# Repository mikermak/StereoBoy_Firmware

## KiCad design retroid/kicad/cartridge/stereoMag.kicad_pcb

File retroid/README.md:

# StereoBoy – Retroid build

A ready-to-order build of [iamericmin's StereoBoy](https://github.com/iamericmin/StereoBoy_Firmware) ([Hackaday](https://hackaday.io/project/205771-stereoboy)), prepared in October 2026. **Not ordered yet** — this folder holds everything needed to pick it up again.

## What changed compared to the original

| Area | Change |
|---|---|
| Firmware | `src/hw_config.c` reads the cartridge SD card over **SPI1** (CS = GPIO2), matching the published StereoMag cartridge. SDIO stays available with `-DSB_SD_SDIO=ON`. Prebuilt: [`firmware/StereoBoy_FW_sd-spi.uf2`](firmware/) (builds, not yet tested on hardware). |
| Board look | White solder mask + JLCPCB **multi-colour silkscreen**: black board, red tracks, gold pads. Signatures, quote, bear logo and "ENGINEERING PROTOTYPE" removed; **RETROID** logo added on both sides, plus a "based on StereoBoy by iamericmin" credit. Electrically unchanged (KiCad DRC: 0 unconnected, 0 schematic-parity issues). |
| KiCad | [`kicad/hoofdprint/`](kicad/hoofdprint/) is the branded main board (KiCad 10). The drill/place origin is set to the board's bottom-left corner so the Gerbers line up with the EasyEDA colour files. |
| Parts | BOM fixed against the designer's own parts lists. Notable: TPS61090 (not TPS61092), SN74HC165**PWR** (TSSOP footprint), FM24**CL**64B (3.3 V), APX803S-31, VS1053B. Out-of-stock parts replaced (see `BESTELLEN.md`). |

## Folder contents

- `productie/hoofdprint/gerbers_hoofdprint_KLEUR.zip` – KiCad Gerbers + the four `Fabrication_Colorful*` files from EasyEDA Pro. Upload this one.
- `productie/hoofdprint/JLCPCB_BOM.csv`, `JLCPCB_CPL.csv` – 70 BOM lines / 184 placements, every line has a verified LCSC number. VR1 (thumb wheel) and D17 (RGB LED) are left out on purpose (hand-solder / optional).
- `productie/cartridge/` – StereoMag dev-kit cartridge (2 layers, 1.0 mm): Gerbers, BOM, CPL.
- `artwork/` – 1200 dpi colour artwork (exact board size), previews, the RETROID wordmark, outline DXFs, and the EasyEDA colour files.
- `scripts/` – how the artwork was made: KiCad SVG plots → PNG (`colorart.py`, `colorart_brand.py`), and `origin_dxf.py` (aux origin + outline DXF).
- `BESTELLEN.md` – step-by-step JLCPCB checklist (Dutch).
- `StereoBoy_bestellijst.xlsx` – full parts list, cartridge, enclosure/donor-GBP parts, known issues (Dutch).

## JLCPCB settings that matter

4 layers · **1.0 mm** · White · **ENIG 1U** · min via **0.2 mm** · Advanced Options → Silkscreen Technology → **EasyEDA multi-color silkscreen** · Confirm Production File: Yes · PCBA Standard, **both sides**, qty 2, Confirm Parts Placement: Yes. Tick J7 (USB-C) by hand in the BOM step — JLC deselects it ("processing difficult").

Quote on 1 Oct 2026: **$387.77** (PCB $84.83 + PCBA $302.94, excl. shipping). Most of it is one-off cost (setup, stencil, fixture, ~$107 extended-part feeder fees), so 5 assembled boards cost far less per unit than 2. Swapping ~10 passives to JLC "Basic" parts would save roughly $25–35.

## Still open

- **Music library script.** The firmware expects `.artists.sbc` / `.albums.sbc` / `.tracks.sbc` (+ `artwork.lut/bin`) on the SD card; the generator script is not in the original repo.
- Colour silkscreen + KiCad Gerbers is not an official JLC flow: check the colours in JLC's production-file preview before approving.
- Cartridge DRC: I2S_WSEL/BCLK swapped at the 2×10 dev header and the reset RC unconnected — harmless unless J2 is used.

## Licensing note

The upstream repository has no licence file. The cartridge KiCad files come from the designer's [Hackaday files page](https://hackaday.io/project/205771/files). All credit for the hardware and firmware goes to iamericmin and team; RETROID branding is ours.

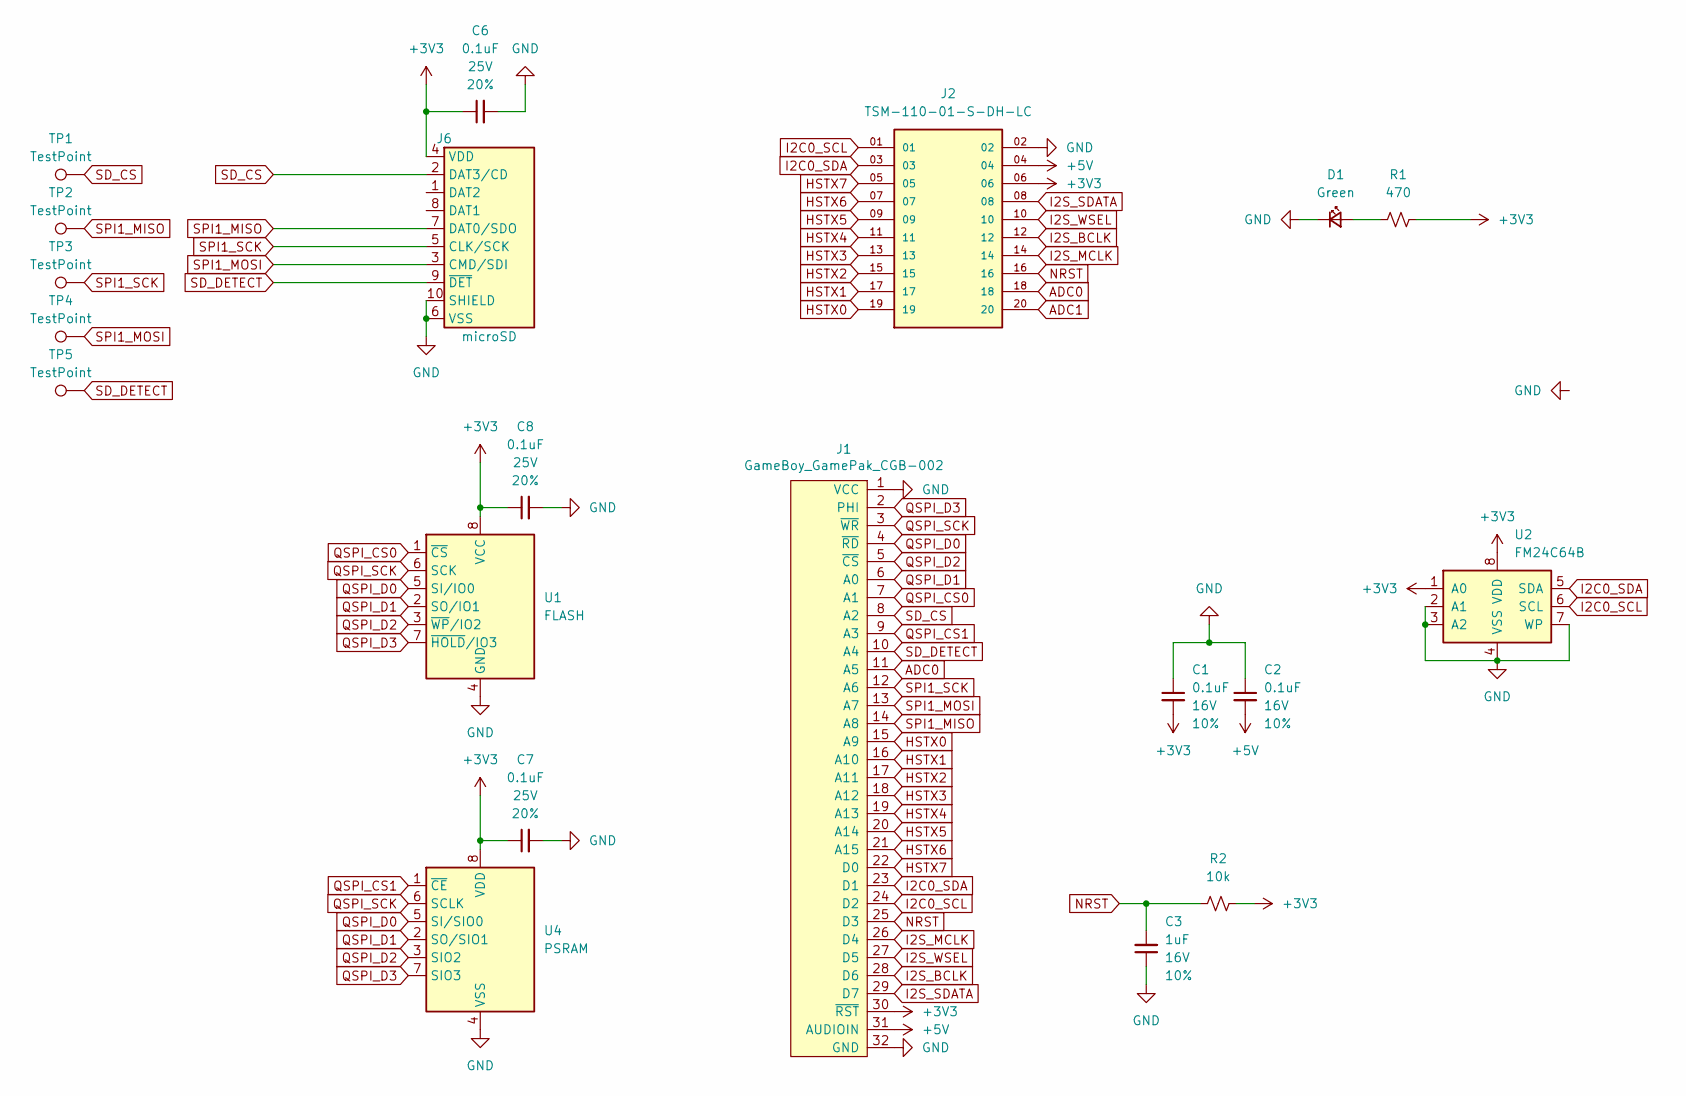
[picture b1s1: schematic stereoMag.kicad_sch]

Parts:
C1, C2: 0.1uF; C_1206_3216Metric; Voltage 16V; Tolerance 10%
C3: 1uF; C_0603_1608Metric; Voltage 16V; Tolerance 10%
C6, C7, C8: 0.1uF; C_0603_1608Metric; Voltage 25V; Tolerance 20%
D1: Green; LED_0603_1608Metric_Green
J1: GameBoy_GamePak_CGB-002; GameBoy_GamePak_CGB-002_P1.50mm_Edge
J2: TSM-110-01-S-DH-LC; SAMTEC_TSM-110-01-S-DH-LC; PARTREV R
J6: microSD; microSD_External_Pin
R1: 470; R_0603_1608Metric
R2: 10k; R_0603_1608Metric
TP1, TP2, TP3, TP4, TP5: TestPoint; TestPoint_Pad_D1.0mm
U1: FLASH; SOIC-8_3.9x4.9mm_P1.27mm
U2: FM24C64B; SOIC-8_3.9x4.9mm_P1.27mm
U4: PSRAM; SOIC-8_3.9x4.9mm_P1.27mm

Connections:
+3V3: C1.2, C6.1, C7.1, C8.1, J1.30 (~RST), J2.06, J6.4 (VDD), R1.2, R2.2, U1.8 (VCC), U2.1 (A0), U2.8 (VDD), U4.8 (VDD)
+5V: C2.2, J1.31 (AUDIOIN), J2.04
ADC0: J1.11 (A5), J2.18
ADC1: J2.20
GND: C1.1, C2.1, C3.1, C6.2, C7.2, C8.2, D1.1 (K), J1.1 (VCC), J1.32 (GND), J2.02, J6.6 (VSS), J6.10 (SHIELD), U1.4 (GND), U2.2 (A1), U2.3 (A2), U2.4 (VSS), U2.7 (WP), U4.4 (VSS)
HSTX0: J1.15 (A9), J2.19
HSTX1: J1.16 (A10), J2.17
HSTX2: J1.17 (A11), J2.15
HSTX3: J1.18 (A12), J2.13
HSTX4: J1.19 (A13), J2.11
HSTX5: J1.20 (A14), J2.09
HSTX6: J1.21 (A15), J2.07
HSTX7: J1.22 (D0), J2.05
I2C0_SCL: J1.24 (D2), J2.01, U2.6 (SCL)
I2C0_SDA: J1.23 (D1), J2.03, U2.5 (SDA)
I2S_BCLK: J1.28 (D6), J2.12
I2S_MCLK: J1.26 (D4), J2.14
I2S_SDATA: J1.29 (D7), J2.08
I2S_WSEL: J1.27 (D5), J2.10
NRST: C3.2, J1.25 (D3), J2.16, R2.1
unnamed: D1.2 (A), R1.1
QSPI_CS0: J1.7 (A1), U1.1 (~CS)
QSPI_CS1: J1.9 (A3), U4.1 (~CE)
QSPI_D0: J1.4 (~RD), U1.5 (SI/IO0), U4.5 (SI/SIO0)
QSPI_D1: J1.6 (A0), U1.2 (SO/IO1), U4.2 (SO/SIO1)
QSPI_D2: J1.5 (~CS), U1.3 (~WP/IO2), U4.3 (SIO2)
QSPI_D3: J1.2 (PHI), U1.7 (~HOLD/IO3), U4.7 (SIO3)
QSPI_SCK: J1.3 (~WR), U1.6 (SCK), U4.6 (SCLK)
SD_CS: J1.8 (A2), J6.2 (DAT3/CD), TP1.1
SD_DETECT: J1.10 (A4), J6.9 (~DET), TP5.1
SPI1_MISO: J1.14 (A8), J6.7 (DAT0/SDO), TP2.1
SPI1_MOSI: J1.13 (A7), J6.3 (CMD/SDI), TP4.1
SPI1_SCK: J1.12 (A6), J6.5 (CLK/SCK), TP3.1

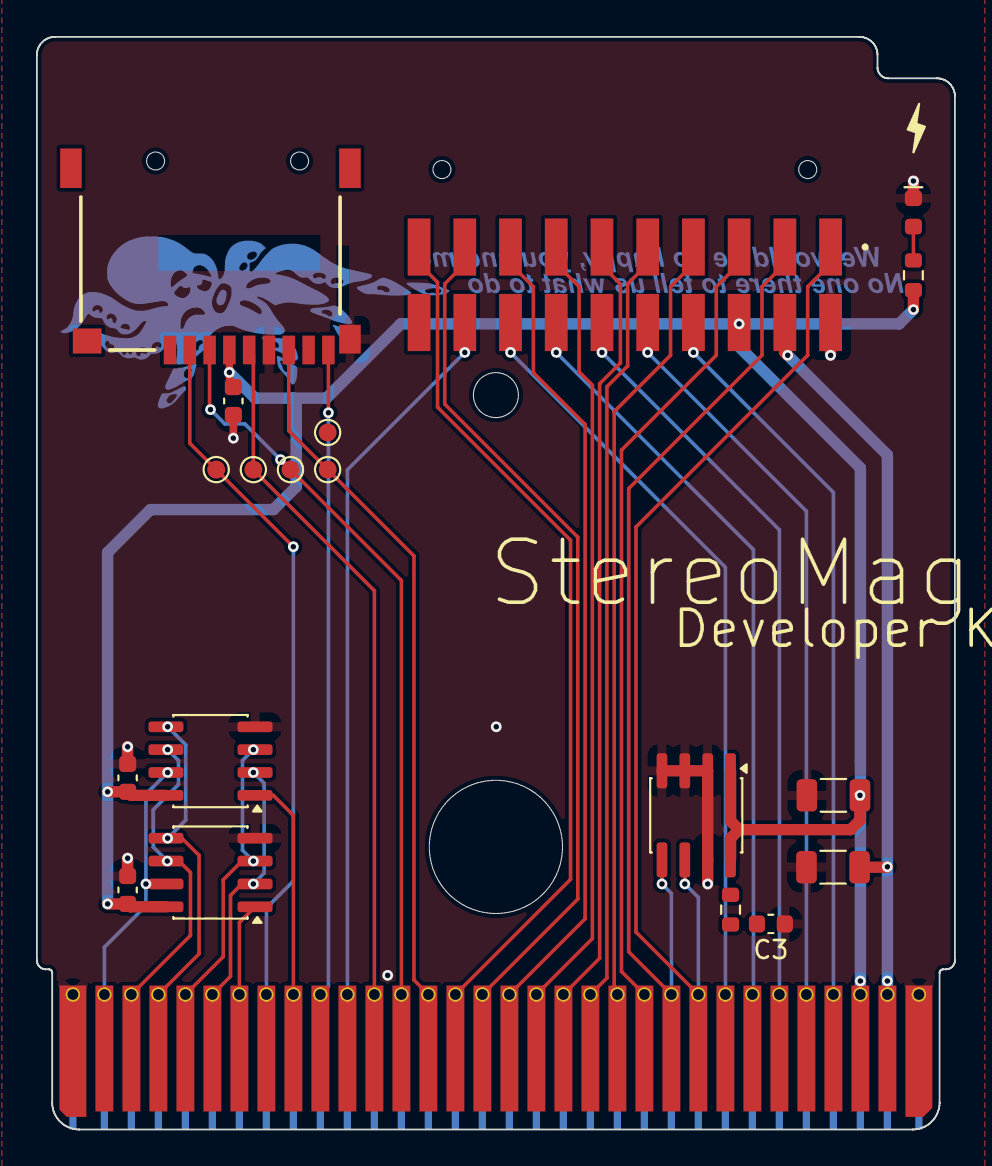
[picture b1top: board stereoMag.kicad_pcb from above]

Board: 2 copper layers, 51.0 x 60.7 mm, 20 parts (0 on the bottom side), 32 nets.

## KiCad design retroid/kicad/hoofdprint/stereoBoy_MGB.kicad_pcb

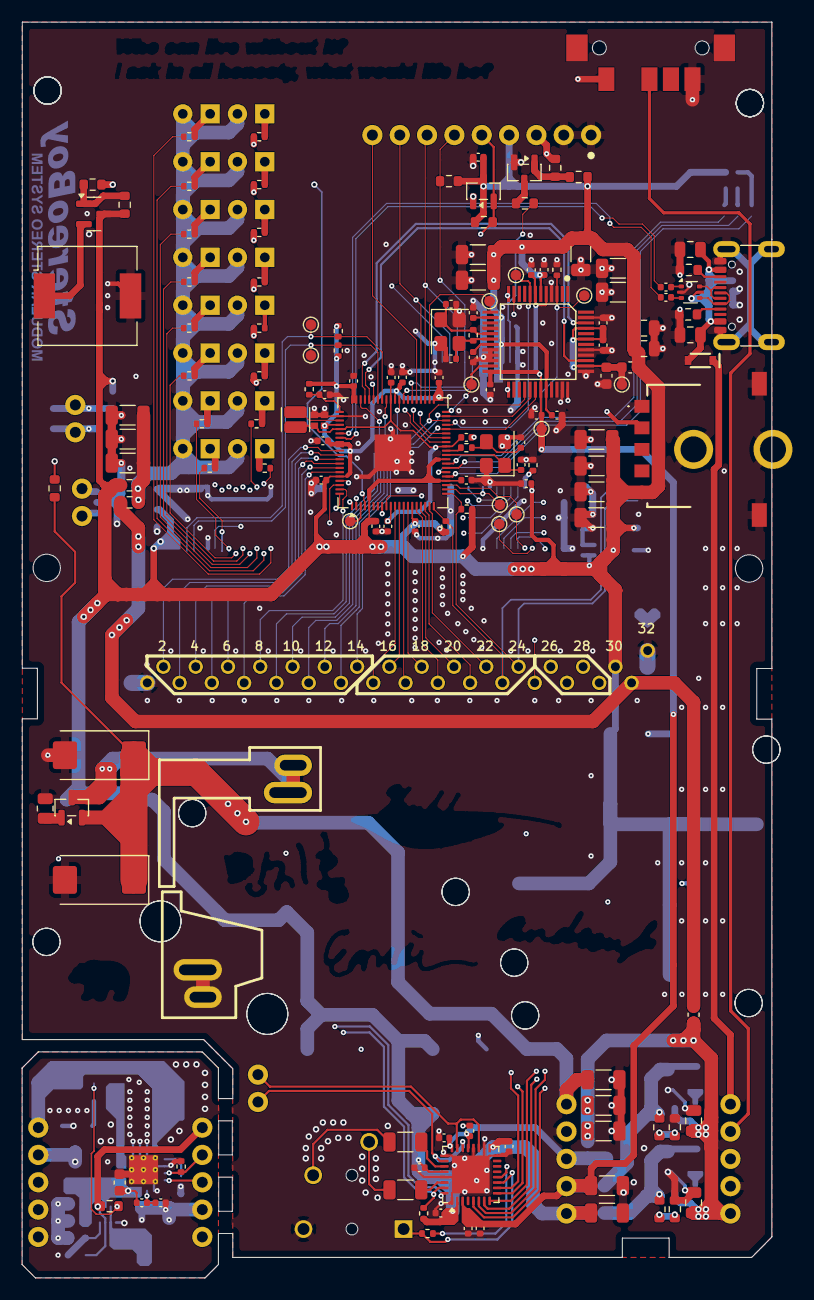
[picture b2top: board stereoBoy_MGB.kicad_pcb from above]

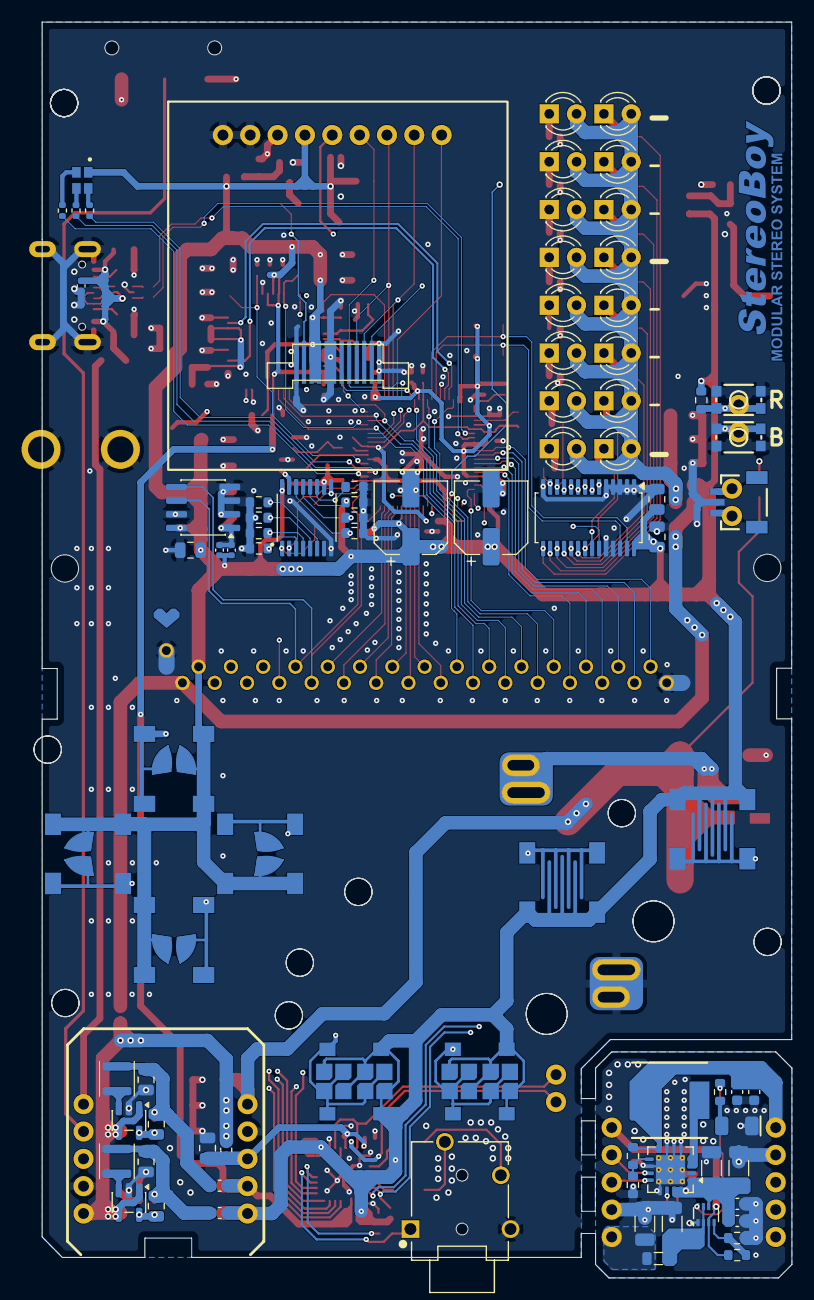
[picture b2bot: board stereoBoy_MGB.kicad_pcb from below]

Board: 4 copper layers, 69.7 x 116.7 mm, 249 parts (84 on the bottom side), 165 nets.

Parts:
+0: MGB+BATTERY4
-0: MGB-BATTERY4
BTN_A1: GameBoy_ButtonPad; GameBoy_A_B_Pad
BTN_B1: GameBoy_ButtonPad; GameBoy_A_B_Pad
BTN_D1: GameBoy_ButtonPad; GameBoy_DPad
BTN_L1: GameBoy_ButtonPad; GameBoy_DPad
BTN_R1: GameBoy_ButtonPad; GameBoy_DPad
BTN_U1: GameBoy_ButtonPad; GameBoy_DPad
BZ1: Buzzer; Buzzer_CUI_CPT-9019S-SMT
C1: 100uF; CP_EIA-7343-15_Kemet-W_HandSolder
C2: 47uF; CP_EIA-7343-15_Kemet-W_HandSolder
C3, C4: 10pF; C_0402_1005Metric
C5, C6, C15, C16, C17, C18, C19, C22, C23, C25, C26, C37, C47, C49, C52, C57, C58, C60, C75, C79: 0.1uF; C_0402_1005Metric
C7, C54, C85: 0.1uF; C_0603_1608Metric
C8: 10uF; C_1206_3216Metric
C9, C11: 4.7uF; C_0805_2012Metric
C10, C12: 6.8pF; C_0805_2012Metric
C13, C24, C27, C31, C36, C38, C39, C40, C41, C71: 1.0uF; C_0402_1005Metric
C14: 4.7uF; C_0402_1005Metric
C20, C21: 15pF; C_0402_1005Metric
C28: 100uF; C_0603_1608Metric
C29, C61, C64, C68, C69, C76, C87: 1.0uF; C_0805_2012Metric
C30, C86: 10uF; C_0805_2012Metric
C32, C33, C48, C53, C62, C77, C78, C80: 100uF; C_1206_3216Metric
C34, C42, C45, C46, C51, C55, C56, C66, C67, C70, C72, C73, C74, C88: 1.0uF; C_1206_3216Metric
C43, C44: 10uF; CP_Elec_6.3x4.5
C59: 0.1uF; C_0805_2012Metric
C63: 2.2uF; C_0603_1608Metric
C65: 10uF; C_0603_1608Metric
C81: 0.1uF; WAi_0402_1005Metric
C82: 4.7uF; WAi_0402_1005Metric
C83, C84: 22.1uF; C_0402_1005Metric
D1, D2, D3, D4, D5, D6, D7, D8, D9, D10, D11, D12, D13, D14, D15, D16: LED; LED_D3.0mm
D17: CLMVC-FKA-CL1D1L71BB7C3C3; CREE_LED_2mm_x_2mm_Common_Anode
D22: BAT60JFILM; SOD-323
D23: Green; LED_1206_3216Metric_Green
J1: Conn_01x12; 1.54_IPS_FPC_Solder
J2: JST_1mm_3_Vertical; JST_1x03_P1.0mm_Horizontal_SMD
J3: GameBoy_Cartridge; MGB-CART-CONN
J4, J8: Conn_01x02; 1x02_P2.54mm
J5: SJ-43514; SJ_43514
J6: Conn_01x09; 1x09_P2.54mm
J7: USB_C_Receptacle_USB2.0_16P; USB_C_Receptacle_GCT_USB4105-xx-A_16P_TopMnt_Horizontal
J10, J11: Conn_01x05; 1x05_P2.54mm
J13: Conn_01x10; StereoBoy_PSU
L1: 6.8uH; Inductor_7.3x6.6mm
L2, L6, L8: 600Ω @ 100MHz; C_0603_1608Metric
L3, L7: 600Ω @ 100MHz; L_0603_1608Metric
L4, L5: 2.2uH; L_APV_ANR3012
L9: 3.3uH; L_Cenker_CKCS201610
L10: 600Ω @ 100MHz; L_0805_2012Metric
Q1: DMG2301L; SOT-23
Q2: FDN306P; SOT-23
Q3: BSS138; SOT-23
R1: 500k; R_0603_1608Metric
R2: 330; R_0603_1608Metric
R3: 390k; R_0603_1608Metric
R4: 1.62M; C_0402_1005Metric
R5, R6, R7, R8, R9, R10, R11, R12, R20, R24, R27, R29, R34, R39: 10k; R_0603_1608Metric
R13: 180k; C_0402_1005Metric
R14, R15: 27; C_0402_1005Metric
R16, R33: 5.1k; R_0603_1608Metric
R17, R18, R19: 330; R_0402_1005Metric
R21, R22, R23: 0; R_0603_1608Metric
R25: 33; R_0402_1005Metric
R26, R49: 1k; R_0402_1005Metric
R28: 10; R_0603_1608Metric
R30, R54: 10K; R_0402_1005Metric
R31: 1k; R_0603_1608Metric
R32, R58, R59, R60, R61, R62, R63, R64, R65, R66, R67, R68, R69, R70, R71, R72: 220; R_0402_1005Metric
R35: 453k; R_0603_1608Metric
R36, R38: 100k; R_0603_1608Metric
R37: 200k; R_0603_1608Metric
R44: 100k; R_0805_2012Metric
R45, R46, R47, R48: 2.2K; R_0402_1005Metric
R50: 100K; R_0402_1005Metric
R51: 1M; R_0402_1005Metric
R53: 2.2k; R_0402_1005Metric
R55, R56: 1.4M; R_0603_1608Metric
R73: 220; R_0603_1608Metric
SELECT1: SMD_6x3.5mm_h2.5mm; GameBoy_Select_Start
SPK_CONN1: Conn_01x02; 1x02
START1: SMD_6x3.5mm_h2.5mm; GameBoy_Select_Start
SW1, SW2: SMD_4.6x2.8mm_h2.5mm; Push_SMD_4.6x2.8mm_h2.5mm
SW3: MGB-SW1; GBP_Power_Switch
TP1, TP2, TP10, TP12, TP23, TP24, TP26, TP27, TP31, TP32, TP33: TestPoint_Alt; TestPoint_Pad_D1.0mm
TP14: TestPoint; TestPoint_Pad_D1.0mm
U1: CODECODER-VS1053B_LQFP48_; VS1053b
U2: PCA9685PW; TSSOP-28_4.4x9.7mm_P0.65mm
U3: TPS61090; Texas_RSA_VQFN-16-1EP_4x4mm_P0.65mm_EP2.7x2.7mm_ThermalVias
U4, U8: TLV62569DBV; SOT-23-5
U5: APX803; SOT-23
U6: 74HC165; TSSOP-16_4.4x5mm_P0.65mm
U7: TPS2116DRL; SOT-583-8
U10: TLV320AIC3100; VQFN-32-1EP_5x5mm_P0.5mm_EP3.5x3.5mm
U11: RP2350B; QFN-80-1EP_10x10mm_P0.4mm_EP3.4x3.4mm
U12: USBLC6-2P6; SOT-666
U14: FM24C64C; SOIC-8_3.9x4.9mm_P1.27mm
UNK_HOLE_0: dummyfp0
UNK_HOLE_1: dummyfp1
UNK_HOLE_4: dummyfp4
UNK_HOLE_5: dummyfp5
UNK_HOLE_6: dummyfp6
UNK_HOLE_7: dummyfp7
UNK_HOLE_8: dummyfp8
UNK_HOLE_9: dummyfp9
UNK_HOLE_10: dummyfp10
UNK_HOLE_11: dummyfp11
UNK_HOLE_12: dummyfp12
VR1: RK10J11R0A0L
Y1, Y2: 12MHz; Crystal_SMD_3225-4Pin_3.2x2.5mm

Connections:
+1V2: C22.1, C23.1, C25.1, C82.1, L9.1, U11.10 (DVDD), U11.32 (DVDD), U11.51 (DVDD), U11.65 (VREG_FB)
+1V8: C24.2, C26.2, C31.2, C39.2, C40.2, C80.1, J13.2, L6.2, TP26.1, U1.5 (CVDD0), U1.7 (CVDD1), U1.24 (CVDD2), U1.31 (CVDD3), U10.3 (DVDD)
+3V3: BTN_A1.1, BTN_B1.1, BTN_D1.1, BTN_L1.1, BTN_R1.1, BTN_U1.1, C6.2, C13.2, C15.2, C16.1, C17.1, C18.1, C19.1, C27.2, C29.2, C36.2, C37.2, C38.2, C41.2, C43.1, C44.1, C46.2, C47.1, C51.2, C52.1, C55.2, C57.1, C58.1, C59.1, C60.1, C61.2, C64.1, C66.2, C67.2, C69.2, C70.2, C71.2, C72.2, C73.2, C74.2, C78.1, C79.1, C81.2, D17.1, J1.3, J1.4, J3.30 (~RES), J6.6, J13.1, L2.2, L8.1, Q1.3 (D), R20.2, R22.1, R24.1, R25.1, R27.2, R29.2, R30.2, R34.1, R45.2, R46.1, R47.2, R48.1, SELECT1.1, START1.1, U1.6 (IOVDD0), U1.14 (IOVDD1), U1.19 (IOVDD2), U1.32 (XTEST), U2.28 (VDD), U5.3 (VCC), U6.16 (VCC), U10.2 (IOVDD), U10.17 (AVDD), U10.28 (HPVDD), U11.5 (IOVDD), U11.15 (IOVDD), U11.24 (IOVDD), U11.29 (IOVDD), U11.41 (IOVDD), U11.50 (IOVDD), U11.59 (ADC_AVDD), U11.60 (IOVDD), U11.64 (VREG_VIN), U11.68 (USB_OTP_VDD), U11.69 (QSPI_IOVDD), U11.76 (IOVDD), U14.8 (VDD), VR1.3 (CW)
+5V: J3.31 (VIN), L7.1, R21.2
+5V_BUCK: C7.1, C28.1, C48.1, C62.1, C63.1, R4.1, U3.1 (VOUT), U3.15 (VOUT), U3.16 (VOUT), U7.6 (VIN2)
+5V_OUT: C9.1, C11.1, C53.2, C77.1, J13.6, L3.2, L7.2, U4.1 (EN), U4.4 (VIN), U8.1 (EN), U8.4 (VIN)
+5V_OUT_MODULE: C42.1, J10.1, L10.2
+5V_SPK: C83.1, C84.1, C87.2, J13.3, L3.1, U10.21 (SPKVDD), U10.24 (SPKVDD)
+BATT: C1.1, C2.1, C34.2, J13.5, Q2.2 (S), R23.1
+BATT_MODULE: C65.1, C85.1, J11.5, L1.2, R1.1, U3.8 (VBAT)
+VCC_LED: C45.2, C56.2, C88.2, D1.2 (A), D2.2 (A), D3.2 (A), D4.2 (A), D5.2 (A), D6.2 (A), D7.2 (A), D8.2 (A), D9.2 (A), D10.2 (A), D11.2 (A), D12.2 (A), D13.2 (A), D14.2 (A), D15.2 (A), D16.2 (A), R21.1, R22.2
ADC0: J3.11 (A5), U11.49 (ADC0/GPIO40)
AVDD: C49.1, C54.1, C75.1, L8.2, TP10.1, U1.38 (AVDD0), U1.43 (AVDD1), U1.45 (AVDD2)
BACKLIGHT: J6.7, R31.2, U11.2 (GPIO5)
BTN_A: BTN_A1.2, R5.2, U6.13 (D2)
BTN_B: BTN_B1.2, R6.2, U6.14 (D3)
BTN_D: BTN_D1.2, R8.2, U6.4 (D5)
BTN_L: BTN_L1.2, R9.2, U6.6 (D7)
BTN_R: BTN_R1.2, R10.2, U6.3 (D4)
BTN_SELECT: R11.2, SELECT1.2, U6.12 (D1)
BTN_START: R12.2, START1.2, U6.11 (D0)
BTN_U: BTN_U1.2, R7.2, U6.5 (D6)
BUZZER: R2.1, U11.4 (GPIO7)
CODEC_DREQ: TP31.1, U1.8 (DREQ), U11.37 (GPIO29)
CODEC_L_OUT: U1.46 (LEFT), U11.57 (ADC6/GPIO46)
CODEC_RST: R50.1, TP27.1, U1.3 (XRESET), U11.28 (GPIO27)
CODEC_R_OUT: U1.39 (RIGHT), U11.56 (ADC5/GPIO45)
CODEC_XCS: TP33.1, U1.23 (XCS), U11.40 (GPIO32)
CODEC_XDCS: TP32.1, U1.13 (XDCS/BSYNC1), U11.42 (GPIO33)
DAC_GPIO1: U10.32 (GPIO1), U11.80 (GPIO3)
DAC_RST: R30.1, U10.31 (~RESET), U11.78 (GPIO1)
GND: -0.P$1, -0.P$3, -0.P$4, BZ1.2 (-), C1.2, C2.2, C3.1, C4.1, C5.1, C6.1, C7.2, C8.2, C9.2, C11.2, C13.1, C14.2, C15.1, C16.2, C17.2, C18.2, C19.2, C20.1, C21.1, C22.2, C23.2, C24.1, C25.2, C26.1, C27.1, C28.2, C29.1, C30.2, C31.1, C34.1, C36.1, C37.1, C38.1, C39.1, C40.1, C41.1, C42.2, C43.2, C44.2, C45.1, C46.1, C47.2, C48.2, C49.2, C51.1, C52.2, C53.1, C54.2, C55.1, C56.1, C57.2, C58.2, C59.2, C60.2, C61.1, C62.2, C63.2, C64.2, C65.2, C66.1, C67.1, C68.2, C69.1, C70.1, C71.1, C72.1, C73.1, C74.1, C75.2, C76.2, C77.2, C78.2, C79.2, C80.2, C81.1, C82.2, C83.2, C84.2, C85.2, C86.2, C87.1, C88.1, D23.1 (K), J1.1, J1.5, J1.6, J1.12, J2.2, J3.1 (VCC), J3.32 (GND), J5.4, J6.8, J6.9, J7.A1 (GND), J7.A12 (GND), J7.B1 (GND), J7.B12 (GND), J7.S1 (SHIELD), J10.2, J11.4, J13.4, J13.7, Q3.2 (S), R3.2, R5.1, R6.1, R7.1, R8.1, R9.1, R10.1, R11.1, R12.1, R13.2, R16.2, R33.2, R36.2, R38.2, R44.1, R49.2, R50.2, R54.2, R56.2, SW1.1, SW2.1, SW3.P$3 (3), U1.4 (DGND0), U1.16 (DGND1), U1.20 (DGND2), U1.21 (DGND3), U1.22 (DGND4), U1.35 (GND), U1.37 (AGND0), U1.40 (AGND1), U1.41 (AGND2), U1.47 (AGND3), U2.1 (A0), U2.2 (A1), U2.3 (A2), U2.4 (A3), U2.5 (A4), U2.14 (VSS), U2.24 (A5), U2.25 (EXTCLK), U3.5 (PGND), U3.6 (PGND), U3.7 (PGND), U3.10 (SYNC), U3.13 (GND), U3.17 (PAD), U4.2 (GND), U5.1 (GND), U6.8 (GND), U6.10 (DS), U7.1 (GND), U8.2 (GND), U10.1 (IOVSS), U10.16 (AVSS), U10.18 (DVSS), U10.20 (SPKVSS), U10.25 (SPKVSS), U10.29 (HPVSS), U10.33 (EP), U11.62 (VREG_PGND), U12.2 (GND), U14.1 (A0), U14.2 (A1), U14.3 (A2), U14.4 (VSS), U14.7 (WP), VR1.1 (CCW), VR1.6 (MP1), VR1.7 (MP2), VR1.8 (MH1), VR1.9 (MH2), Y1.2, Y1.4, Y2.2, Y2.4
HP_L: C32.2, J5.2
HP_R: C33.1, J5.3
HSTX_12: J3.15 (A9), U11.11 (GPIO12)
HSTX_13: J3.16 (A10), U11.12 (GPIO13)
HSTX_14: J3.17 (A11), U11.13 (GPIO14)
HSTX_15: J3.18 (A12), U11.14 (GPIO15)
HSTX_16: J3.19 (A13), U11.16 (GPIO16)
HSTX_17: J3.20 (A14), U11.17 (GPIO17)
HSTX_18: J3.21 (A15), U11.18 (GPIO18)
HSTX_19: J3.22 (D0), U11.19 (GPIO19)
I2C0_SCL: J3.24 (D2), R48.2, U10.10 (SCL), U11.21 (GPIO21), U14.6 (SCL)
I2C0_SDA: J3.23 (D1), R47.1, U10.9 (SDA), U11.20 (GPIO20), U14.5 (SDA)
I2C1_SCL: R46.2, TP1.1, U2.26 (SCL), U11.54 (ADC3/GPIO43)
I2C1_SDA: R45.1, TP2.1, U2.27 (SDA), U11.53 (ADC2/GPIO42)
I2S_BCLK: J3.28 (D6), U1.11 (GPIO6/I2S_SCLK3), U10.7 (BCLK)
I2S_DIN: J3.29 (D7), U1.12 (GPIO7/I2S_SDATA3), U10.5 (DIN)
I2S_MCLK: J3.26 (D4), U1.25 (GPIO/I2S_MCLK3), U10.8 (MCLK)
I2S_WSEL: J3.27 (D5), U1.36 (GPIO4/I2S-LROUT3), U10.6 (WCLK)
LEDDRV_OE: U2.23 (~OE), U11.77 (GPIO0)
LEDK: J1.2, R28.2
LOW_BATT: J13.8, U11.8 (GPIO10)
LOW_BATT_MODULE: J10.3, U3.12 (LBO)
MICBIAS: R53.2, U10.12 (MICBIAS)
MICDET: J5.1, R53.1, U10.11 (VOL/MICDET)
NRST: J3.25 (D3), J4.1, R27.1, SW1.2, U11.35 (RUN)
unnamed: BZ1.1 (+), Q1.2 (S)
unnamed: C8.1, L10.1, U7.2 (VOUT), U7.7 (VOUT)
unnamed: C10.1, C30.1, L2.1, L4.2, R35.1
unnamed: C12.1, C86.1, L5.2, L6.1, R37.1
unnamed: C21.2, R26.1, Y2.3
unnamed: D1.1 (K), R32.2
unnamed: D2.1 (K), R58.2
unnamed: D3.1 (K), R59.2
unnamed: D4.1 (K), R60.2
unnamed: D5.1 (K), R61.2
unnamed: D6.1 (K), R62.2
unnamed: D7.1 (K), R63.2
unnamed: D8.1 (K), R64.2
unnamed: D9.1 (K), R65.2
unnamed: D10.1 (K), R66.2
unnamed: D11.1 (K), R67.2
unnamed: D12.1 (K), R68.2
unnamed: D13.1 (K), R69.2
unnamed: D14.1 (K), R70.2
unnamed: D15.1 (K), R71.2
unnamed: D16.1 (K), R72.2
unnamed: D17.2, R17.1
unnamed: D17.3, R18.1
unnamed: D17.4, R19.1
unnamed: D23.2 (A), R73.1
unnamed: J7.A5 (CC1), R16.1
unnamed: J7.B5 (CC2), R33.1
unnamed: L1.1, U3.3 (SW), U3.4 (SW)
unnamed: Q1.1 (G), R2.2, R20.1
unnamed: +0.P$1, +0.P$2, +0.P$3, Q2.3 (D)
unnamed: Q2.1 (G), R44.2
unnamed: Q3.3 (D), R28.1
unnamed: Q3.1 (G), R29.1, R31.1
unnamed: R14.2, U12.1 (I/O1)
unnamed: R15.2, U12.3 (I/O2)
unnamed: SPK_CONN1.1, U10.22 (SPKP), U10.26 (SPKP)
unnamed: SPK_CONN1.2, U10.19 (SPKM), U10.23 (SPKM)
unnamed: R23.2, SW3.P$1 (1)
unnamed: C4.2, R51.1, U1.18 (XTALI), Y1.3
unnamed: C3.2, R51.2, U1.17 (XTALO), Y1.1
unnamed: R32.1, U2.6 (LED0)
unnamed: R58.1, U2.7 (LED1)
unnamed: R59.1, U2.8 (LED2)
unnamed: R60.1, U2.9 (LED3)
unnamed: R61.1, U2.10 (LED4)
unnamed: R62.1, U2.11 (LED5)
unnamed: R63.1, U2.12 (LED6)
unnamed: R64.1, U2.13 (LED7)
unnamed: R65.1, U2.15 (LED8)
unnamed: R66.1, U2.16 (LED9)
unnamed: R67.1, U2.17 (LED10)
unnamed: R68.1, U2.18 (LED11)
unnamed: R69.1, U2.19 (LED12)
unnamed: R70.1, U2.20 (LED13)
unnamed: R71.1, U2.21 (LED14)
unnamed: R72.1, U2.22 (LED15)
unnamed: R4.2, R13.1, U3.14 (FB)
unnamed: R1.2, R3.1, U3.9 (LBI)
unnamed: C10.2, R35.2, R36.1, U4.5 (FB)
unnamed: L4.1, U4.3 (SW)
unnamed: R49.1, U6.15 (~CE)
unnamed: R55.2, R56.1, U7.4 (PR1)
unnamed: R39.1, R73.2, U7.8 (ST)
unnamed: C12.2, R37.2, R38.1, U8.5 (FB)
unnamed: L5.1, U8.3 (SW)
unnamed: C32.1, U10.27 (HPL)
unnamed: C33.2, U10.30 (HPR)
unnamed: TP14.1, U11.3 (GPIO6)
unnamed: C14.1, R25.2, U11.61 (VREG_AVDD)
unnamed: L9.2, U11.63 (VREG_LX)
unnamed: C20.2, U11.30 (XIN), Y2.1
unnamed: R26.2, U11.31 (XOUT)
POT: U11.55 (ADC4/GPIO44), VR1.2 (WIPER)
PWR_EN: J13.9, SW3.P$C (C)
PWR_EN_MODULE: J10.4, R54.1, U3.11 (EN)
QSPI_CS: J3.7 (A1), J4.2, SW2.2, U11.75 (QSPI_~CS)
QSPI_CS1: J3.9 (A3), U11.58 (ADC7/GPIO47)
QSPI_IO0: J3.4 (~RD), U11.72 (QSPI_SD0)
QSPI_IO1: J3.6 (A0), U11.74 (QSPI_SD1)
QSPI_IO2: J3.5 (~CS), U11.73 (QSPI_SD2)
QSPI_IO3: J3.2 (PHI), U11.70 (QSPI_SD3)
QSPI_SCK: J3.3 (~WR), U11.71 (QSPI_SCLK)
RGB_B: R17.2, U11.27 (GPIO26)
RGB_G: R18.2, U11.26 (GPIO25)
RGB_R: R19.2, U11.25 (GPIO24)
SD_CS: J3.8 (A2), U11.79 (GPIO2)
SD_DETECT: J3.10 (A4), U11.52 (ADC1/GPIO41)
SPI0_CS: J1.8, J6.4, R24.2, U11.46 (GPIO37)
SPI0_MISO: J6.1, U11.45 (GPIO36)
SPI0_MOSI: J1.10, J6.2, U11.44 (GPIO35)
SPI0_SCK: J1.9, J6.3, U11.43 (GPIO34)
SPI1_MISO: J3.14 (A8), U1.30 (SO), U11.36 (GPIO28)
SPI1_MOSI: J3.13 (A7), U1.29 (SI), U11.39 (GPIO31)
SPI1_SCK: J3.12 (A6), U1.28 (SCLK), U11.38 (GPIO30)
SR_CLK: TP24.1, U6.2 (CP), U11.23 (GPIO23)
SR_OUT: TP12.1, U6.9 (Q7), U11.22 (GPIO22)
SR_SH/LD: TP23.1, U6.1 (~PL), U11.9 (GPIO11)
SWCLK: J2.1, J8.2, U11.33 (SWCLK)
SWDIO: J2.3, J8.1, U11.34 (SWDIO)
TFTDC_3V: J1.7, U11.48 (GPIO39)
TFTRST_3V: J1.11, J6.5, R34.2, U5.2 (RESET), U11.1 (GPIO4)
USB_DM: J7.A7 (D-), J7.B7 (D-), U12.4 (I/O2)
USB_DM_STM32: R15.1, U11.66 (USB_D-)
USB_DP: J7.A6 (D+), J7.B6 (D+), U12.6 (I/O1)
USB_DP_STM32: R14.1, U11.67 (USB_D+)
VBUS: D22.1 (K), J13.10
VBUS_MODULE: J10.5, R39.2, R55.1, U7.3 (VIN1), U7.5 (MODE)
VBUS_RAW: C5.2, C68.1, C76.1, D22.2 (A), J7.A4 (VBUS), J7.A9 (VBUS), J7.B4 (VBUS), J7.B9 (VBUS), U12.5 (VBUS)
